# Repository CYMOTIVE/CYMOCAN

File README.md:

# CYMOCAN USB-CAN Interface #

CYMOCAN is a low cost USB to CAN-FD (Controller Area Network - Flexible Data rate) interface.

Using the [CandleLight firmware](https://github.com/candle-usb/candleLight_fw) CYMOCAN can work with Windows(WCID USB) and Linux(SocketCAN over gs_usb).

## What is in this repository?

* Hardware files for the CYMOCAN board and [Debug edge](https://debug-edge.io/) breakout board

## Hardware
## CYMOCAN_G0
CYMOCAN_G0 has:
* 2 CAN-FD interfaces 
* USB
* SWD + UART (Over [Debug edge](https://debug-edge.io/))

CYMOCAN_G0 BOM
|Reference|Description|Quantity|
|:---|:---:|:---:|
| C1, C2 | 0603 1uF Capacitor | 2
| C3| 0603 0.1uF Capacitor | 1
| C4 | 0603 100nf Capacitor | 1
| C5 | 0603 4.7uF Capacitor | 1
| D1, D2, D3, D4, D5, D6 | 0603 LED | 6
| J1 | Molex 105450-0101 USB-C socket | 1
| J2, J3, J4, J7 | 01x02 Pin Header | 4
| J5, J8 | 3 Pin TerminalBlock Bornier 5.08mm | 2
| R1, R2 | 0603 5.1K Resistor | 2
| R3, R4 | 0603 10K Resistor | 2
| R5 | 0603 40K Resistor | 1
| R6, R7, R8, R9, R13 | 0603 220 Resistor | 5
| R10, R11 | 0603 120 Resistor | 2
| R12 | 0603 330 Resistor | 1
| SW1 | Push switch 6mm THT | 1
| U1 | AP2112K-3.3 LDO regulator| 1
| U2 | STM32G0B1CBT6 Microcontroller | 1
| U3, U5 | TJA1051T-3 CAN transceiver | 2
| U4 | USBLC6-2P6 USB ESD protection diodes| 1

## Debug edge breakout
You Do not need this in order to flash and use the CYMOCAN board.
This breakout is only necessary if you wish to debug the board during development. 

## Getting started with CYMOCAN ##
### Flashing the Board ###
After assembling the device follow the flashing instructions in the [CandleLight firmware](https://github.com/candle-usb/candleLight_fw) Repo.

For now use the PR https://github.com/candle-usb/candleLight_fw/pull/139 and the nucleo_g0b1re target.

### Linux ###
You will need to compile a kernel version 5.18 or above for GS_USB CAN-FD support.
The flags you must enable are:
* CAN
* CAN_GS_USB

After compiling and installing the Kernel the CYMOCAN will appear as a standard SocketCAN device.

To setup the device for classic CAN use the following commands
```
sudo ip link set can0 qlen 1000
sudo ip link set can0 up type can bitrate 500000
```
Subsitute can0 for the channel you are using.
Now you can use the device with any SocketCAN compatible software.

### Windows ###
TODO

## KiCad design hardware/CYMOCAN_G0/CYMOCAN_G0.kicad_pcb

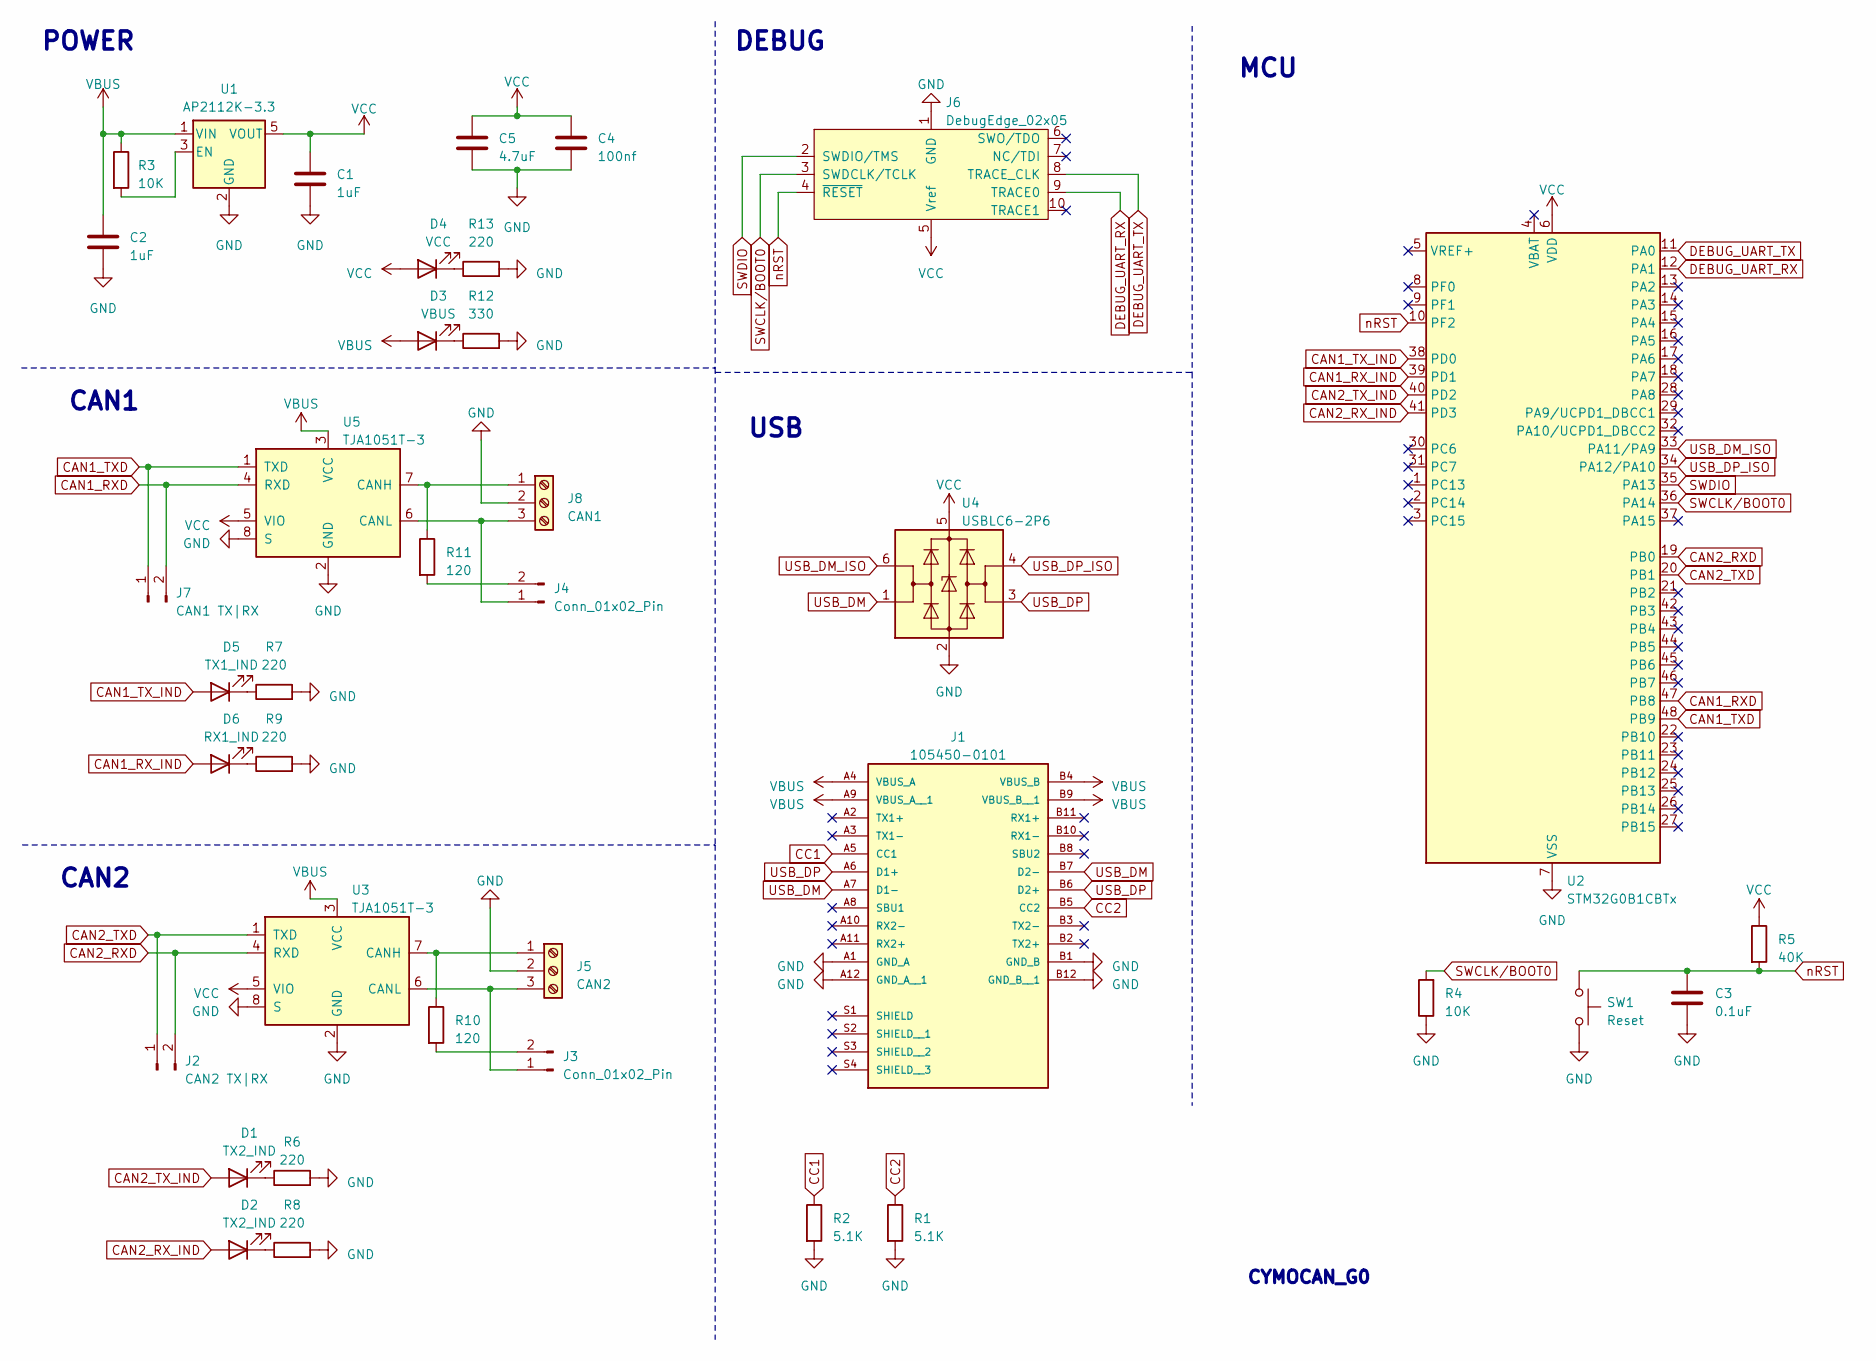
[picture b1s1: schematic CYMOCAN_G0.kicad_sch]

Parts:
C1, C2: 1uF; C_0603_1608Metric_Pad1.08x0.95mm_HandSolder
C3: 0.1uF; C_0603_1608Metric_Pad1.08x0.95mm_HandSolder
C4: 100nf; C_0603_1608Metric_Pad1.08x0.95mm_HandSolder
C5: 4.7uF; C_0603_1608Metric_Pad1.08x0.95mm_HandSolder
D1, D2: TX2_IND; LED_0603_1608Metric_Pad1.05x0.95mm_HandSolder
D3: VBUS; LED_0603_1608Metric_Pad1.05x0.95mm_HandSolder
D4: VCC; LED_0603_1608Metric_Pad1.05x0.95mm_HandSolder
D5: TX1_IND; LED_0603_1608Metric_Pad1.05x0.95mm_HandSolder
D6: RX1_IND; LED_0603_1608Metric_Pad1.05x0.95mm_HandSolder
J1: 105450-0101; MOLEX_105450-0101; PARTREV A7
J2: CAN2 TX|RX; PinHeader_2x01_P2.54mm_Vertical
J3, J4: Conn_01x02_Pin; PinHeader_2x01_P2.54mm_Vertical
J5: CAN2; TerminalBlock_bornier-3_P5.08mm
J6: DebugEdge_02x05; DebugEdge_2x05_Target
J7: CAN1 TX|RX; PinHeader_2x01_P2.54mm_Vertical
J8: CAN1; TerminalBlock_bornier-3_P5.08mm
R1, R2: 5.1K; R_0603_1608Metric_Pad0.98x0.95mm_HandSolder
R3, R4: 10K; R_0603_1608Metric_Pad0.98x0.95mm_HandSolder
R5: 40K; R_0603_1608Metric_Pad0.98x0.95mm_HandSolder
R6, R7, R8, R9, R13: 220; R_0603_1608Metric_Pad0.98x0.95mm_HandSolder
R10, R11: 120; R_0603_1608Metric_Pad0.98x0.95mm_HandSolder
R12: 330; R_0603_1608Metric_Pad0.98x0.95mm_HandSolder
SW1: Reset; SW_PUSH_6mm
U1: AP2112K-3.3; SOT-23-5
U2: STM32G0B1CBTx; LQFP-48_7x7mm_P0.5mm
U3, U5: TJA1051T-3; SOIC-8_3.9x4.9mm_P1.27mm
U4: USBLC6-2P6; SOT-666

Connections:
CAN1_RXD: J7.2, U2.47 (PB8), U5.4 (RXD)
CAN1_RX_IND: D6.2 (A), U2.39 (PD1)
CAN1_TXD: J7.1, U2.48 (PB9), U5.1 (TXD)
CAN1_TX_IND: D5.2 (A), U2.38 (PD0)
CAN2_RXD: J2.2, U2.19 (PB0), U3.4 (RXD)
CAN2_RX_IND: D2.2 (A), U2.41 (PD3)
CAN2_TXD: J2.1, U2.20 (PB1), U3.1 (TXD)
CAN2_TX_IND: D1.2 (A), U2.40 (PD2)
CC1: J1.A5 (CC1), R2.1
CC2: J1.B5 (CC2), R1.1
DEBUG_UART_RX: J6.9 (TRACE0), U2.12 (PA1)
DEBUG_UART_TX: J6.8 (TRACE_CLK), U2.11 (PA0)
GND: C1.2, C2.2, C3.2, C4.2, C5.2, J1.A1 (GND_A), J1.A12 (GND_A__1), J1.B1 (GND_B), J1.B12 (GND_B__1), J5.2, J6.1 (GND), J8.2, R1.2, R2.2, R4.1, R6.2, R7.2, R8.2, R9.2, R12.2, R13.2, SW1.2, U1.2 (GND), U2.7 (VSS), U3.2 (GND), U3.8 (S), U4.2 (GND), U5.2 (GND), U5.8 (S)
unnamed: D1.1 (K), R6.1
unnamed: D2.1 (K), R8.1
unnamed: D3.1 (K), R12.1
unnamed: D4.1 (K), R13.1
unnamed: D5.1 (K), R7.1
unnamed: D6.1 (K), R9.1
unnamed: J3.1, J5.3, U3.6 (CANL)
unnamed: J3.2, R10.2
unnamed: J4.1, J8.3, U5.6 (CANL)
unnamed: J4.2, R11.2
unnamed: J5.1, R10.1, U3.7 (CANH)
unnamed: J8.1, R11.1, U5.7 (CANH)
unnamed: R3.2, U1.3 (EN)
SWCLK/BOOT0: J6.3 (SWDCLK/TCLK), R4.2, U2.36 (PA14)
SWDIO: J6.2 (SWDIO/TMS), U2.35 (PA13)
USB_DM: J1.A7 (D1-), J1.B7 (D2-), U4.1 (I/O1)
USB_DM_ISO: U2.33 (PA11/PA9), U4.6 (I/O1)
USB_DP: J1.A6 (D1+), J1.B6 (D2+), U4.3 (I/O2)
USB_DP_ISO: U2.34 (PA12/PA10), U4.4 (I/O2)
VBUS: C2.1, D3.2 (A), J1.A4 (VBUS_A), J1.A9 (VBUS_A__1), J1.B4 (VBUS_B), J1.B9 (VBUS_B__1), R3.1, U1.1 (VIN), U3.3 (VCC), U5.3 (VCC)
VCC: C1.1, C4.1, C5.1, D4.2 (A), J6.5 (Vref), R5.1, U1.5 (VOUT), U2.6 (VDD), U3.5 (VIO), U4.5 (VBUS), U5.5 (VIO)
nRST: C3.1, J6.4 (~RESET), R5.2, SW1.1, U2.10 (PF2)

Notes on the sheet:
CAN1
USB
MCU
DEBUG
POWER
CYMOCAN_G0
CAN2

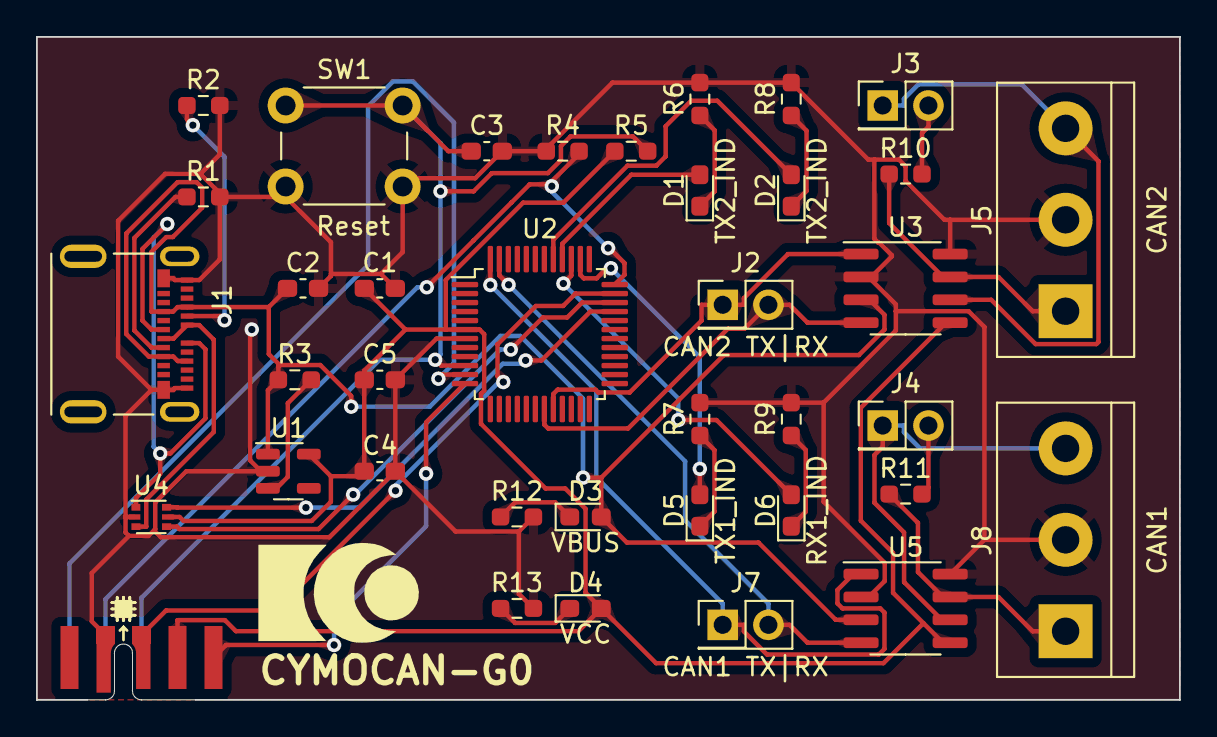
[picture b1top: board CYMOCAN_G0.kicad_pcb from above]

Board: 2 copper layers, 63.5 x 36.8 mm, 38 parts (0 on the bottom side), 35 nets.

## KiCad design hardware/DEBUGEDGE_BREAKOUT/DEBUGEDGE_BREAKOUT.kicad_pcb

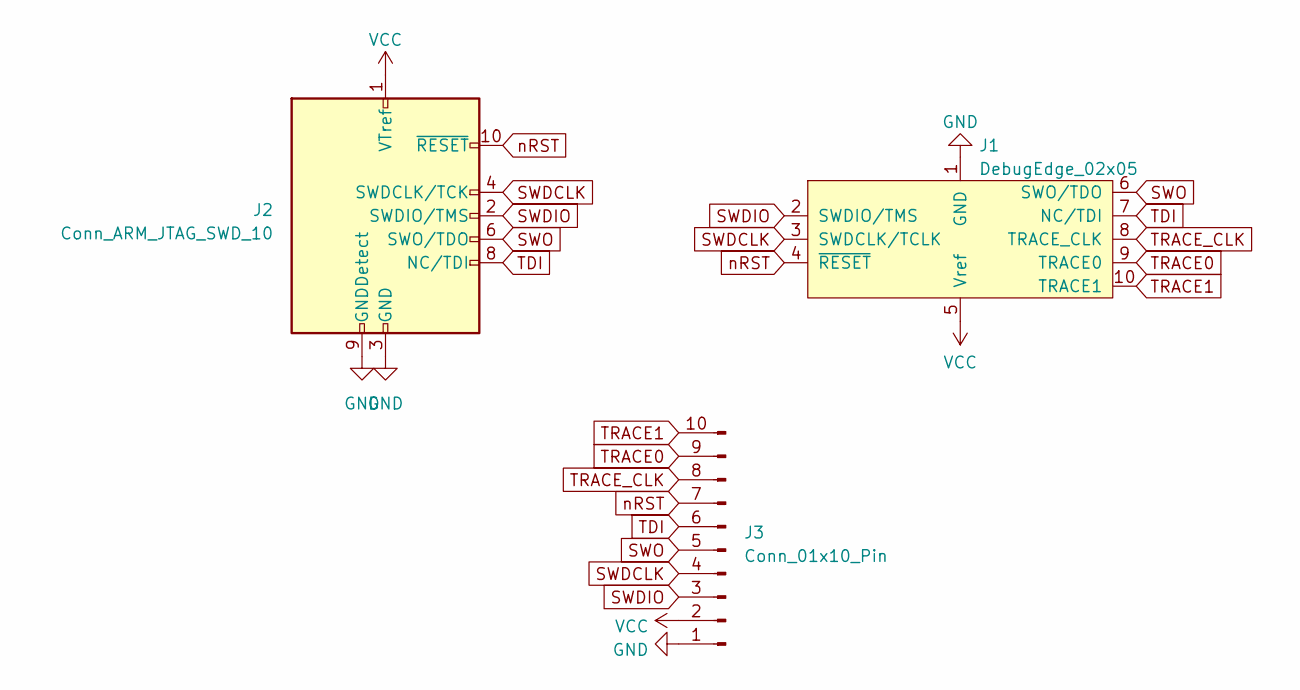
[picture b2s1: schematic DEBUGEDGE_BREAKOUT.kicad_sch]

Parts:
J1: DebugEdge_02x05; DebugEdge_2x05_Host
J2: Conn_ARM_JTAG_SWD_10; PinHeader_2x05_P1.27mm_Vertical_SMD
J3: Conn_01x10_Pin; PinHeader_1x10_P2.54mm_Vertical

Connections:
GND: J1.1 (GND), J2.3 (GND), J2.5 (GND), J2.9 (GNDDetect), J3.1
SWDCLK: J1.3 (SWDCLK/TCLK), J2.4 (SWDCLK/TCK), J3.4
SWDIO: J1.2 (SWDIO/TMS), J2.2 (SWDIO/TMS), J3.3
SWO: J1.6 (SWO/TDO), J2.6 (SWO/TDO), J3.5
TDI: J1.7 (NC/TDI), J2.8 (NC/TDI), J3.6
TRACE0: J1.9 (TRACE0), J3.9
TRACE1: J1.10 (TRACE1), J3.10
TRACE_CLK: J1.8 (TRACE_CLK), J3.8
VCC: J1.5 (Vref), J2.1 (VTref), J3.2
nRST: J1.4 (~RESET), J2.10 (~RESET), J3.7

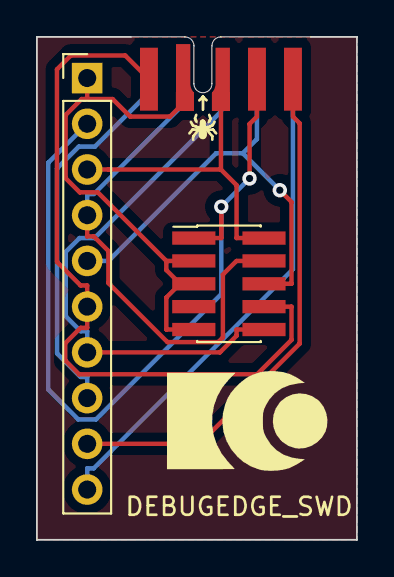
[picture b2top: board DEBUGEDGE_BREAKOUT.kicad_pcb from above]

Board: 2 copper layers, 17.8 x 27.9 mm, 3 parts (0 on the bottom side), 10 nets.

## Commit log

2023-04-18 Add Kicad files to .gitignore
2023-04-18 Initial work on schema
2023-04-18 Update .gitignore Kicad files
2023-06-02 Updated terminal block and footprints
2023-06-04 Layout complete
2023-06-12 Fix DRC issues and Restructure
2023-06-12 Fix DRC issues
2023-06-12 Add DebugEdge Breakout board
2023-06-13 Adjust JLC placeholder
2023-06-13 Fix footprints and jlc placeholder in DebugEdge Breakout
2023-06-28 Fix Led Resistor values
2023-06-28 Added License
2023-06-28 Fix typo in D2 LED label
